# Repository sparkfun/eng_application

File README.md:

SparkFun Quality Assurance Specialist Application
============================================
The Rob Reynolds Edition
------------------------

I just wanted to say a quick thank you for your time and consideration. I truly appreciate it.
We now return you to your regularly scheduled README file.

----------------------------

This repository is used to vet candidates for the Quality Assurance Specialist Application

Users will demonstrate basic version control skills, and provide code, writing, and project samples.

How to use this repository
--------------------------

1. Fork this repository.
2. Follow the instructions in the `README` files contained within each top level directory.
3. Send a pull request back to SparkFun.

Note that pull requests can either be sent back to the main repository or you can create a branch on your fork and create a pull request into master on your fork. 
**The latter method requires that you contact the hiring manager of the position with a link to your pull request, and affords you as an applicant some degree of anonymity.**

What Happens To Your Pull Request
----------------------------------

Your pull request will *never* be merged (to keep this repository open for the applicants that use it after you). 
When you've either been hired or declined your pull request will simply be closed.

During the review process you may find comments applied to your pull request - asking questions, seeking clarification, a rogue compliment, etc.

Legal Stuff Regarding Your Pull Request
---------------------------------------

**No content from your pull request will be used by SparkFun Electronics for any purpose other than assessing the quality of a given applicant.**

We won't rip off your work. You retain copyright on any pull request you submit.

However, by submitting a pull request, you affirm that the content within is solely your original work. 
Content generated collaboratively with other individuals must be identified as such and content generated entirely by other individuals should **not** be included. 
Failure to meet these guidelines may result in disqualification as an applicant.

About the Company
------------------
[SparkFun Electronics](https://www.sparkfun.com) is an online shop for the do-it-yourself electronics enthusiast. 
Our customers include inventors, artists, students, hobbyists, and just plain curious individuals looking for some fun tinkering with electronics.

SparkFun is also very committed to bringing electronics education into the mainstream by curating free educational materials and working with schools and institutions around the country to bring electronics into the classroom. 
Lastly, SparkFun is a staunch advocate of the open source movement, most recently being a leader in Open Source Hardware.

About the Position
------------------
Please see the included position.md file for the job posting.

License Information
-------------------
Please review the LICENSE.md file for license information. 

If you have any questions or concerns on licensing, please contact techsupport@sparkfun.com.

Distributed as-is; no warranty is given.

- Your friends at SparkFun.

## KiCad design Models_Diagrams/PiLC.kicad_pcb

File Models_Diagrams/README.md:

Modeling Samples
================

Included here are several Model Samples. They include a Fritzing layout, along with a couple of 3D builds I've recently completed. (Recently = within the last year.) 

The Fritzing Diagram is for the Singing Nutcracker build that currently sits at my desk. It is the same build for which I've submitted my code sample. Just trying to tie things together here.

The 3D models are from two separate builds. The first will be familiar to Funions, and that's the [Safe Cracking Robot](https://learn.sparkfun.com/tutorials/building-a-safe-cracking-robot). I designed the entire safe in 3D in order to then design the components that would nest onto the safe itself, the dial, and the handle.

The other 3D piece is a build a Marble Machine that I did for fun, and to try to get my kids interested in basic physics. Every step was conceived and designed by me. Consideration for each element was taken not just for 3D design and aesthetic, but also for structural integrity and printability. The Marble Machine is pretty much the physical manifestation of what goes on in my head all the time. Explains a lot.

The design:

The build:

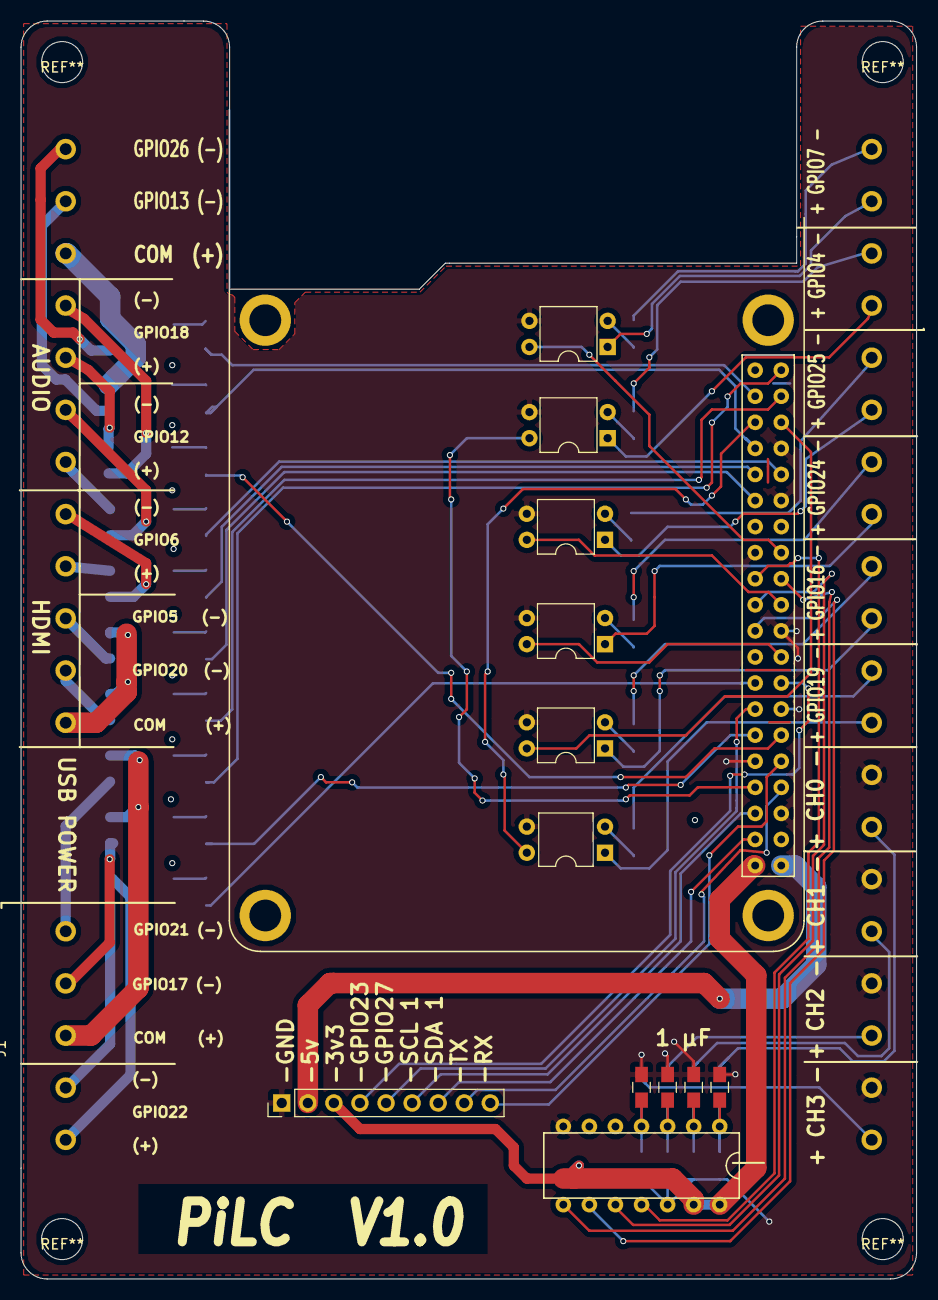
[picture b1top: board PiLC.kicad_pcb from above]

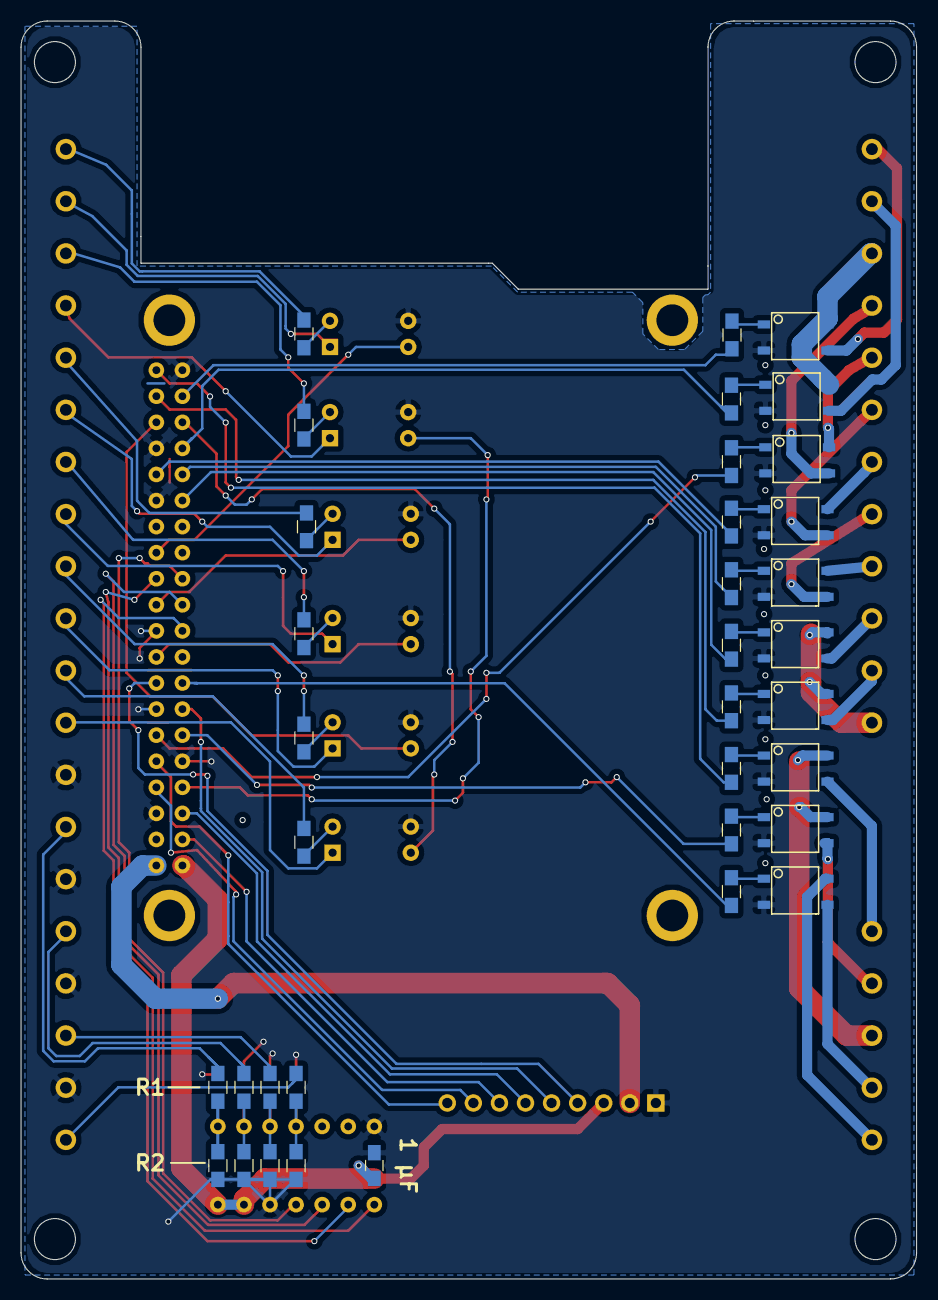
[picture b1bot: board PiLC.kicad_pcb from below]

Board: 2 copper layers, 87.2 x 122.6 mm, 50 parts (35 on the bottom side), 82 nets.

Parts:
C1, C2, C3, C4, C5: C; C_0805_HandSoldering
J1, J3: CONN_01X20; screw_terminal_regular_20x1_5.08mm
J2: Raspberry_Pi_2_3; ras_pi_less_silk
J4: CONN_01X09; Pin_Header_Straight_1x09_Pitch2.54mm
R1: 330; R_0805_HandSoldering
R2, R3, R4, R5, R6, R7, R8, R9, R10, R11, R12, R13, R14, R15, R16: 200; R_0805_HandSoldering
R17, R18, R19, R20, R21, R22, R23, R24: R; R_0805_HandSoldering
U1, U2, U3, U4, U5, U6, U7, U8, U9, U10: G3VM-61GR2; omron_g3vm_61gr2
U11: MCP3204; mcp3204
U12, U13, U14, U15, U16, U17: LTV-814; DIP-4_W7.62mm

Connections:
+3V3: C1.2, J2.1, J4.3, U11.13, U11.14
+5V: J2.2, J4.2
/1-: J1.20, U1.3
/1_2_COM: J1.18, U1.4, U2.4
/2-: J1.19, U2.3
/6-: J1.11, U6.3
/6_7_COM: J1.9, U6.4, U7.4
/7-: J1.10, U7.3
/8-: J1.5, U8.3
/8_9_COM: J1.3, U8.4, U9.4
/9-: J1.4, U9.3
CLK: J2.23, U11.11
DI0: J2.35, U12.4
DI1: J2.36, U13.4
DI2: J2.18, U14.4
DI3: J2.22, U15.4
DI4: J2.7, U16.4
DI5: J2.26, U17.4
DO2: J2.12, R3.2
DO3: J2.32, R4.2
DO4: J2.31, R5.2
DO7: J2.15, R10.2
DO11: J2.37, R1.2
DO12: J2.33, R2.2
DO51: J2.29, R6.2
DO52: J2.38, R7.2
DO61: J2.40, R8.2
DO62: J2.11, R9.2
Exp1: J2.16, J4.4
Exp2: J2.13, J4.5
Exp3: J2.5, J4.6
Exp4: J2.3, J4.7
GND: C1.1, C2.1, C3.1, C4.1, C5.1, J2.6, J2.9, J2.14, J2.20, J2.25, J2.30, J2.34, J2.39, J3.2, J3.4, J3.6, J3.8, J4.1, R18.1, R20.1, R22.1, R24.1, U1.2, U2.2, U3.2, U4.2, U5.2, U6.2, U7.2, U8.2, U9.2, U10.2, U11.7, U11.12, U12.3, U13.3, U14.3, U15.3, U16.3, U17.3
MISO: J2.21, U11.10
MOSI: J2.19, U11.9
unnamed: C2.2, R23.2, R24.2, U11.1
unnamed: C3.2, R19.2, R20.2, U11.3
unnamed: C4.2, R17.2, R18.2, U11.4
unnamed: C5.2, R21.2, R22.2, U11.2
unnamed: J1.1, U10.4
unnamed: J1.2, U10.3
unnamed: J1.12, U5.4
unnamed: J1.13, U5.3
unnamed: J1.14, U4.4
unnamed: J1.15, U4.3
unnamed: J1.16, U3.4
unnamed: J1.17, U3.3
unnamed: J3.1, R17.1
unnamed: J3.3, R19.1
unnamed: J3.5, R21.1
unnamed: J3.7, R23.1
unnamed: J3.9, U12.1
unnamed: J3.10, R11.2
unnamed: J3.11, U13.1
unnamed: J3.12, R12.2
unnamed: J3.13, U14.1
unnamed: J3.14, R13.2
unnamed: J3.15, U15.1
unnamed: J3.16, R14.2
unnamed: J3.17, U16.1
unnamed: J3.18, R15.2
unnamed: J3.19, U17.1
unnamed: J3.20, R16.2
unnamed: R1.1, U1.1
unnamed: R2.1, U2.1
unnamed: R3.1, U3.1
unnamed: R4.1, U4.1
unnamed: R5.1, U5.1
unnamed: R6.1, U6.1
unnamed: R7.1, U7.1
unnamed: R8.1, U8.1
unnamed: R9.1, U9.1
unnamed: R10.1, U10.1
unnamed: R11.1, U12.2
unnamed: R12.1, U13.2
unnamed: R13.1, U14.2
unnamed: R14.1, U15.2
unnamed: R15.1, U16.2
unnamed: R16.1, U17.2
RX: J2.10, J4.9
SS: J2.24, U11.8
TX: J2.8, J4.8

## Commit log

2015-11-25 Updating repository readme
2015-11-25 Adding git files, and license file
2015-11-25 Adding readme instructions for each directory
2015-11-25 Formatting cleanup
2015-11-25 Cleaning up main readme, license file
2015-11-25 Updating department description, adding comp question
2015-12-01 Test
2015-12-01 Update README.md
    Removing test.
2015-12-02 Create Coding Example - Java
    A short example of code I have recently written while learning Java.
2015-12-02 How-To for Operating A Keurig Coffee Maker
    I'm a fraud, I actually made cider while doing this(it was after 9 pm and I would like to sleep tonight).
2015-12-02 Create Warm Fuzzies
    Version 1
2015-12-02 Rename Warm Fuzzies to Warm Fuzzies.wd
2015-12-02 Rename Warm Fuzzies.wd to Warm Fuzzies.md
2015-12-02 Update Warm Fuzzies.md
    Version 1.0.2
    Editing to fix issues with bullets.
2015-12-02 Updated ETC/README.md
2015-12-02 Fixed formatting in ETC/README.md
2015-12-03 Added files to Code/calls
    Fixed formatting of Code/calls/README.md
2015-12-03 Rename WARM_FUZZY_ANSWERS.MD to warm_fuzzy_answers.md
2015-12-03 Add uart library code sample
2015-12-03 Completed Sparkfun application
2015-12-03 PIC Microcontroller GPS Pointer
    This project was created using a template that we used as a starting point for all homeworks and projects the entire semester written by our professor. All code beyond this template was written by my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
2015-12-04 Warm fuzzy answers
2015-12-04 Added solidworks model
2015-12-04 Added todo to model nodes
2015-12-04 Added/edited respective files for application.
2015-12-04 Updated schedule in ETC
2015-12-04 Small formatting change in code comment
2015-12-04 Added Documentation/BrewTea.md
2015-12-04 Added files to the model directory.
    I added ModelInfo.md, OliverSt.skp, and flag.png to this directory.
2015-12-04 Capitalized Inkscape for consistency
2015-12-04 Fixed tabbing in code for improved readability
2015-12-04 Corrected a typo
2015-12-04 Add tutorial to make flavor water.
2015-12-05 Completed Sparkfun Application.
2015-12-05 Fixed formatting error.
2015-12-05 Added code examples
2015-12-05 Added additional documents.
2015-12-06 Updated answer in 'Warm Fuzzies'
2015-12-06 Rename sensing_digital_recorder.md to Sensing_Digital_Recorder.md
2015-12-06 Rename model_sample.md to Model_Sample.md
2015-12-07 Rename README.md to AnsweredQuestions.md
2015-12-07 Code Sample
2015-12-07 typo fix
2015-12-07 hours update
2015-12-07 Create How to Create a Campfire
2015-12-07 Added original README back
    Just in case.
2015-12-07 Rename How to Create a Campfire to HowtoCreateaCampfire.md
2015-12-07 Created Code Sample
2015-12-07 Update README.md
    Typo fix
2015-12-07 GabrielBolivar Application
2015-12-07 Create RGB LED Controller
    This code was written in the Arduino IDE and was originally intended for use with a custom RGB LED strip connected to an ATMEGA328P that I made for the gas tank of my motorcycle. The program has two 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
2015-12-07 Arduino Case
2015-12-07 Questions update
    Questions update
2015-12-07 good night commit
2015-12-07 Warm Fuzzies
2015-12-07 How to Put Your Socks On
2015-12-07 first commit, draft
2015-12-07 Second commit to get other files, draft
2015-12-07 Fixed to add new markdown file and contents
2015-12-07 Removed old file
2015-12-07 Uh oh, duplicate markdown, total mistake
2015-12-07 More changes to Documentation markdown
2015-12-07 Images for Documentation Instructions
2015-12-07 Added an image to test
2015-12-07 Draft, inserting images onto markdown
2015-12-07 More image revisions
2015-12-07 Create ESD_lab4.c
    This code example is from a working code for an 8051 with LCD display. It makes use of C and inline assembly to fully demonstrate LCD functionality on the 8051 architecture.
2015-12-07 Rename WarmFuzzies.txt to WarmFuzzies.md
2015-12-07 Create HowToMakeSoap.md
    Simple documentation of soap making process with tracing example image attribution under Creative Commons.
2015-12-07 The Application of Emily Daub
2015-12-07 Fritzing, aaah, oh dear
2015-12-07 Small changes
2015-12-08 Add blender file and render image as png.
2015-12-08 Add a short programming example
2015-12-08 Added a tutorial on how to exit Vim
2015-12-09 Add all the files from my MasterBlaster java project
2015-12-10 Add a README for the game
2015-12-10 Update Arduino Case
2015-12-10 Add the warm fuzzies README
2015-12-11 added file
2015-12-11 ignore stackdump files
2015-12-11 intital commit
2015-12-11 answered questions
2015-12-11 finished doc
2015-12-11 update word
2015-12-11 update paths
2015-12-12 fix filename
2015-12-12 fix img markdown
2015-12-12 fix img filenames
2015-12-12 proofreading
2015-12-12 update question
2017-05-15 Add files via upload
    This is code for a project I did for the Worlds of Wonder museum in Lafayette, CO. You can also find the project at the link below.
    https://github.com/cmfrancis/WOW-Scanner
2017-05-16 Update README.md
    - Adding instructions for brushing your teeth as an example for documenting and writing a tutorial.
2017-05-16 Update README.md
    adjust image description's format
2017-05-16 Update README.md
    Answering Questions
2017-05-16 Create XBee_ELSequencerV3.ino
    -adding recent project with Sequencer.
2017-05-16 Create XBee_ELSequencer_ControllerV3.ino
    adding wireless controller code
2017-05-16 Rename Code/ELDanceSuit/Arduino/EL_XBeeWirelessControl/XBee_ELSequencerV3/XBee_ELSequencerV3.ino to Code/ELDanceSuit/Arduino/XBee_ELSequencerV3/XBee_ELSequencerV3.ino
2017-05-16 Update README.md
    Modifying description.
2017-05-16 Create LICENSE.md
    -adding licensing for hardware and software.
2017-05-16 Add files via upload
    -Adding example 3D model from the experimental study of thermal convection driven by centrifugal buoyancy in a rapidly rotating annulus.
2017-05-16 Update README.md
    adding description.
2017-05-16 Add files via upload
    -Adding updated resume
2017-05-16 Add files via upload
    Adding Resume
2017-05-16 Add files via upload
    Add image of Toothbrush with Toothpaste.
2017-05-16 Update README.md
    -adding link to image
2017-05-16 Update README.md
    adding examples and licensing.
2017-05-16 Add files via upload
    Saving Images as Assets in case link is temporary.
2017-05-16 Update README.md
    Example of placing images into nice table.
2017-05-17 Add files via upload
    Upload Updated Resume
2017-12-23 updating readme
2017-12-23 updating license date
2017-12-23 creating position.md file with QA specialist job posting
2017-12-23 fixing formatting
2017-12-23 removing unnecessary files
2017-12-26 Established HowToScience.md with table of contents and basic content for each section.
2017-12-26 Added ignores to prevent PyCharm specific files from being added.
2017-12-26 Cleanup
    Removing unnecessary files.
2017-12-27 Images for documentation.
2017-12-27 Cleaning up inconsistent formatting.
2017-12-27 Code
2017-12-27 Model
2017-12-28 QA Specialist Application
2017-12-28 Documentation
2017-12-28 Upload Code Samples
    Updating the README.md, uploading sample Arduino code.
2017-12-28 Sample code and license added
2017-12-28 Update Documentation
    Altering README file and uploading Documentation Sample.
2017-12-28 Update Documentation
    Fixing errors, uploading again.
2017-12-28 Update Documentation
    Fixing errors.
2017-12-28 Update Doxumentation
    Fixing errors.
2017-12-28 adding documentation markdown file
2017-12-28 Updating Documentation
    Fixing errors.
2017-12-28 documentation: added images and links
2017-12-28 Fixed small formatting error
2017-12-28 Adding muscle wire model
2017-12-28 Adding printed model image
2017-12-28 Adding small explanation for model
2017-12-28 Update Documentation
    Fix errors.
2017-12-28 Update files
    Corrections to Documentation and Code.
2017-12-28 Update Documentation
    Make it prettier.
2017-12-28 Uploading files
    Adding multiple files to multiple folders.
2017-12-28 Uploading files
    Uploading 3D files and images.
2017-12-28 Adding 3 files for QA engineering Application.
2017-12-28 Added code and models.
2017-12-28 Cleaning up uncessary files
2017-12-28 Updated language in Documentation.
2017-12-28 Updating files
    Updating and finalizing files. I hope.
2017-12-28 Update files
    Remove old files, update existing files.
2017-12-28 Updating README file
    Yes, Updating README file.
2017-12-28 Small edits to documentation
2017-12-28 final edits to documentation
2017-12-28 Added CC license
2017-12-28 Minor edit to muscle wire explanation
2018-09-19 initial documents for application
2018-09-19 updated gitignore
2018-09-19 applying new gitignore rules
2018-09-19 formatting to doc
2018-09-19 added missing ?
